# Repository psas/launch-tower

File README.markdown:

PSAS Launch Tower Computer (LTC)
================================

PSAS has had three generations of launch tower computers:

- [LTC v1 (2005-2012)](http://psas.pdx.edu/Lv2LaunchTowerElectronics/)
   - PC-104+ 486 running Linux 2.4 talking CAN to PIC18F-based boards with relays and analog
   - Lucent "Wavelan" PCMCIA WiFi card
   - 12V SLA battery powered with 30W solar panel
   - Metal IP66 case on independent
- [LTC v2 (2012 - 2014)](http://psas.pdx.edu/GroundTeamHome/launch_tower_v2/)
   - Beagle board talking USB to Phidget relay and analog boards
   - Alpha WiFi board
   - Ethernet umbilical cord
   - 12V SLA battery powered with 30W solar panel
   - Medium sized plastic IP67 enclosure
- LTC v3
   - BeagleBone Black using GPIO and analog mounted on a single custom carrier PCB
   - 14.7V LiPo pack with solar charger.
   - Smaller case

This repo contains everything related to the launch tower computer
(LTC), with the exception of the userspace software, which is
contained in the [launch-tower-comm repo](https://github.com/psas/launch-tower-comm).

Contents
========

- doc
   - Documentation, what there is of it.

- eagle
   - Schematics and PCB layouts, made with [Eagle](http://www.cadsoftusa.com/).

- laser_cut_drawings
   - Line art of the power and ignition boards' mounting panels, suitable for use with a laser cutter.

- ltc3
   - Everything related to the design and manufacture of the third generation launch tower computer, LTC3.

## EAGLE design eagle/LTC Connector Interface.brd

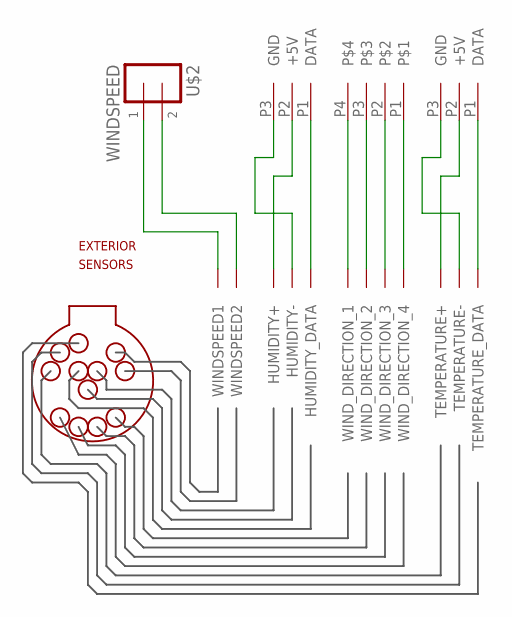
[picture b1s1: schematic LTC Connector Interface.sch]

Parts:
HUMIDITY: MOLEX-3
TEMP: MOLEX-3
U$1: LAYOUT-LEMO-12PIN; LEMO-12
U$2: WINDSPEED; SCREW-TERM-5MM
WINDDIRECTION: MOLEX-4

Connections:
unnamed: U$1.P6 (WINDSPEED1), U$2.1
unnamed: U$1.P5 (WINDSPEED2), U$2.2
unnamed: U$1.P3 (WIND_DIRECTION_3), WINDDIRECTION.P2
unnamed: U$1.P10 (WIND_DIRECTION_2), WINDDIRECTION.P3
unnamed: U$1.P11 (WIND_DIRECTION_1), WINDDIRECTION.P4
unnamed: U$1.P4 (WIND_DIRECTION_4), WINDDIRECTION.P1
unnamed: TEMP.P1 (DATA), U$1.P1 (TEMPERATURE_DATA)
unnamed: TEMP.P3 (GND), U$1.P8 (TEMPERATURE-)
unnamed: TEMP.P2 (+5V), U$1.P7 (TEMPERATURE+)
unnamed: HUMIDITY.P1 (DATA), U$1.P2 (HUMIDITY_DATA)
unnamed: HUMIDITY.P2 (+5V), U$1.P12 (HUMIDITY+)
unnamed: HUMIDITY.P3 (GND), U$1.P9 (HUMIDITY-)

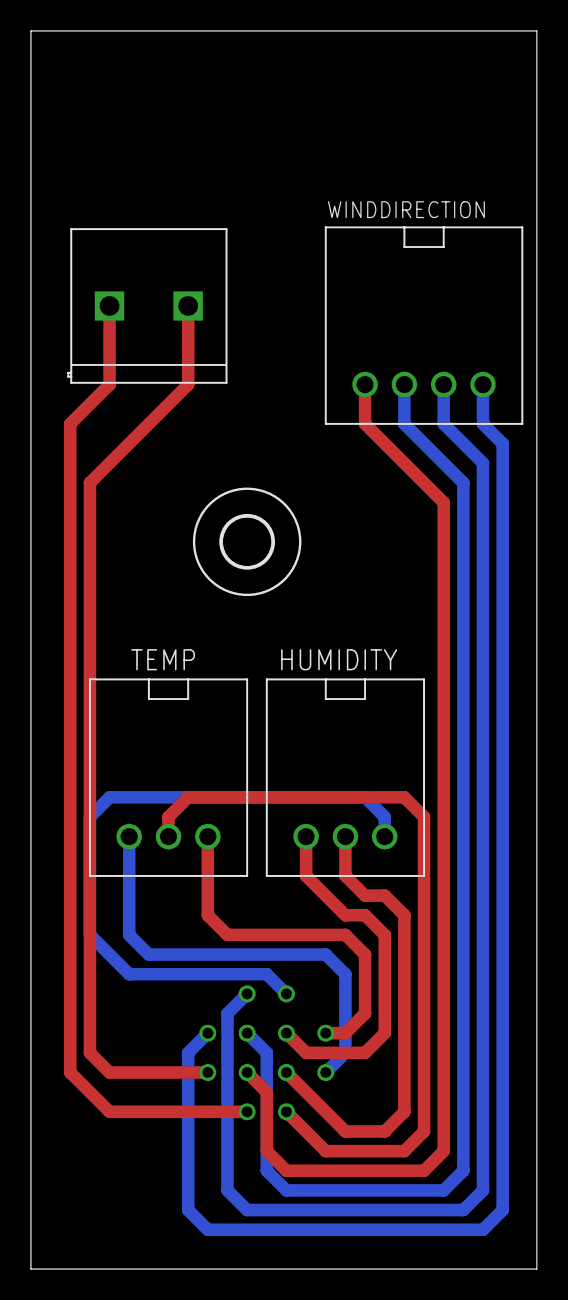
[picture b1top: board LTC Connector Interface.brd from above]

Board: 2 copper layers, 32.7 x 80.0 mm, 6 parts (0 on the bottom side), 12 nets.

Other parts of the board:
U$3: 3,2

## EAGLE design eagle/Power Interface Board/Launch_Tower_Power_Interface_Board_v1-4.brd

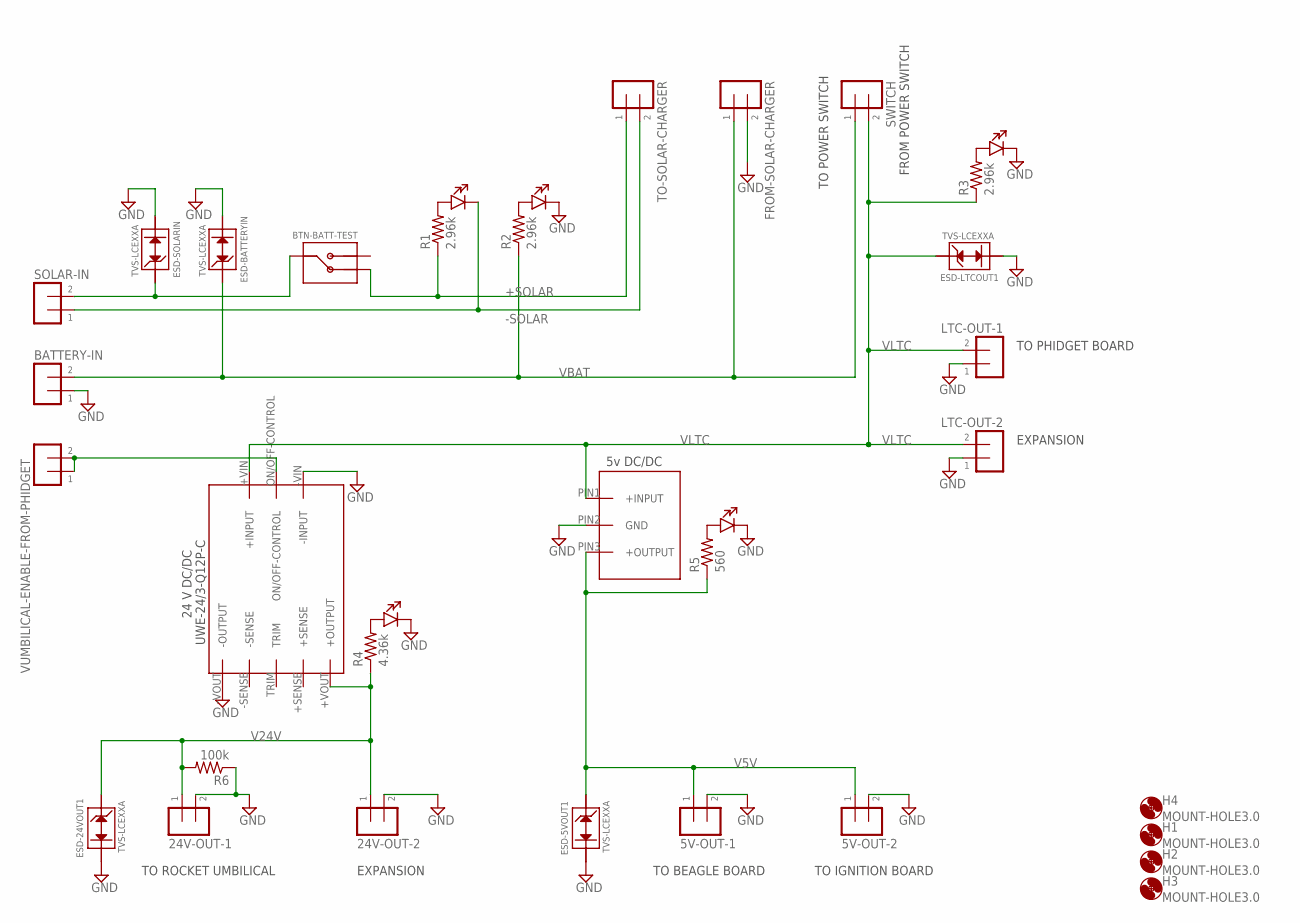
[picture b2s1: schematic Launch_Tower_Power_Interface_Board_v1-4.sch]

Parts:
5V-OUT-1, 5V-OUT-2, 24V-OUT-1, 24V-OUT-2: SCREW-TERMINAL-5MM; SCREW-TERM-5MM
BATTERY-IN: SCREW-TERMINAL-5MM; SCREW-TERM-5MM
BTN-BATT-TEST: BUTTON-107-3006-EVX; BUTTON-1
DC1: DC/DC_CONV_5V; OKI-SIP
DC2: UWE-24/3-Q12P-C; UWE
ESD-5VOUT1, ESD-24VOUT1: TVS-LCEXXA; D0-201
ESD-BATTERYIN: TVS-LCEXXA; D0-201
ESD-LTCOUT1: TVS-LCEXXA; D0-201
ESD-SOLARIN: TVS-LCEXXA; D0-201
FROM-SOLAR-CHARGER: SCREW-TERMINAL-5MM; SCREW-TERM-5MM
H1, H2, H3, H4: MOUNT-HOLE3.0; 3,0
LED-5V-DC/DC, LED-24V-DC/DC: LED-550-XX04; LED-550
LED-BATTERY-IN: LED-550-XX04; LED-550
LED-SOLAR-IN: LED-550-XX04; LED-550
LED-SWITCH-IN: LED-550-XX04; LED-550
LTC-OUT-1, LTC-OUT-2: SCREW-TERMINAL-5MM; SCREW-TERM-5MM
R1, R2, R3: 2.96k; 0805-B
R4: 4.36k; 0805-B
R5: 560; 0805-B
R6: 100k; 0805-B
SOLAR-IN: SCREW-TERMINAL-5MM; SCREW-TERM-5MM
SWITCH: SCREW-TERMINAL-5MM; SCREW-TERM-5MM
TO-SOLAR-CHARGER: SCREW-TERMINAL-5MM; SCREW-TERM-5MM
VUMBILICAL-ENABLE-FROM-PHIDGET: SCREW-TERMINAL-5MM; SCREW-TERM-5MM

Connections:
+SOLAR: BTN-BATT-TEST.NC, R1.1, TO-SOLAR-CHARGER.1
-SOLAR: LED-SOLAR-IN.CATHODE, SOLAR-IN.1, TO-SOLAR-CHARGER.2
GND: 5V-OUT-1.2, 5V-OUT-2.2, 24V-OUT-1.2, 24V-OUT-2.2, BATTERY-IN.1, DC1.PIN2 (GND), DC2.-VIN (-INPUT), DC2.-VOUT (-OUTPUT), ESD-5VOUT1.CATHODE, ESD-24VOUT1.CATHODE, ESD-BATTERYIN.CATHODE, ESD-LTCOUT1.CATHODE, ESD-SOLARIN.CATHODE, FROM-SOLAR-CHARGER.2, LED-5V-DC/DC.CATHODE, LED-24V-DC/DC.CATHODE, LED-BATTERY-IN.CATHODE, LED-SWITCH-IN.CATHODE, LTC-OUT-1.1, LTC-OUT-2.1, R6.1
GPIO: DC2.ON/OFF-CONTROL, VUMBILICAL-ENABLE-FROM-PHIDGET.1, VUMBILICAL-ENABLE-FROM-PHIDGET.2
unnamed: LED-SOLAR-IN.ANODE, R1.2
unnamed: LED-BATTERY-IN.ANODE, R2.2
unnamed: LED-SWITCH-IN.ANODE, R3.2
unnamed: LED-5V-DC/DC.ANODE, R5.2
unnamed: LED-24V-DC/DC.ANODE, R4.2
unnamed: BTN-BATT-TEST.COMMON, ESD-SOLARIN.ANODE, SOLAR-IN.2
V5V: 5V-OUT-1.1, 5V-OUT-2.1, DC1.PIN3 (+OUTPUT), ESD-5VOUT1.ANODE, R5.1
V24V: 24V-OUT-1.1, 24V-OUT-2.1, DC2.+VOUT (+OUTPUT), ESD-24VOUT1.ANODE, R4.1, R6.2
VBAT: BATTERY-IN.2, ESD-BATTERYIN.ANODE, FROM-SOLAR-CHARGER.1, R2.1, SWITCH.1
VLTC: DC1.PIN1 (+INPUT), DC2.+VIN (+INPUT), ESD-LTCOUT1.ANODE, LTC-OUT-1.2, LTC-OUT-2.2, R3.1, SWITCH.2

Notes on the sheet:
5v DC/DC
TO POWER SWITCH
FROM POWER SWITCH
EXPANSION
TO PHIDGET BOARD
TO BEAGLE BOARD
TO IGNITION BOARD
UWE-24/3-Q12P-C
TO ROCKET UMBILICAL
24 V DC/DC

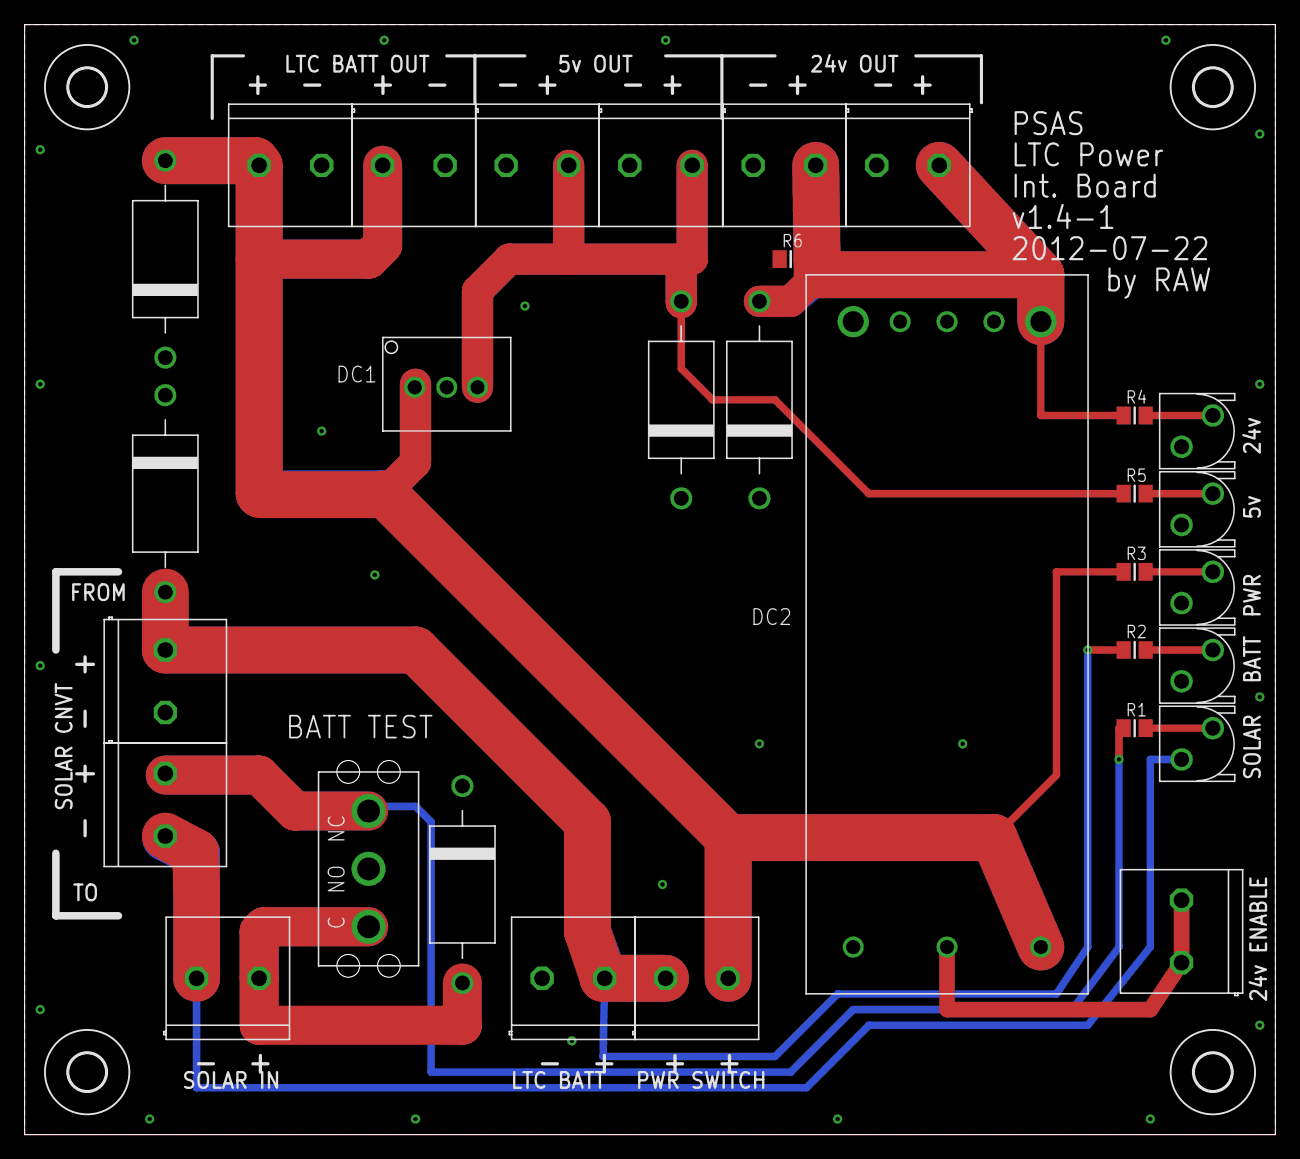
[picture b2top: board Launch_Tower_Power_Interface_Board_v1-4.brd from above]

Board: 2 copper layers, 101.6 x 90.2 mm, 35 parts (0 on the bottom side), 14 nets.

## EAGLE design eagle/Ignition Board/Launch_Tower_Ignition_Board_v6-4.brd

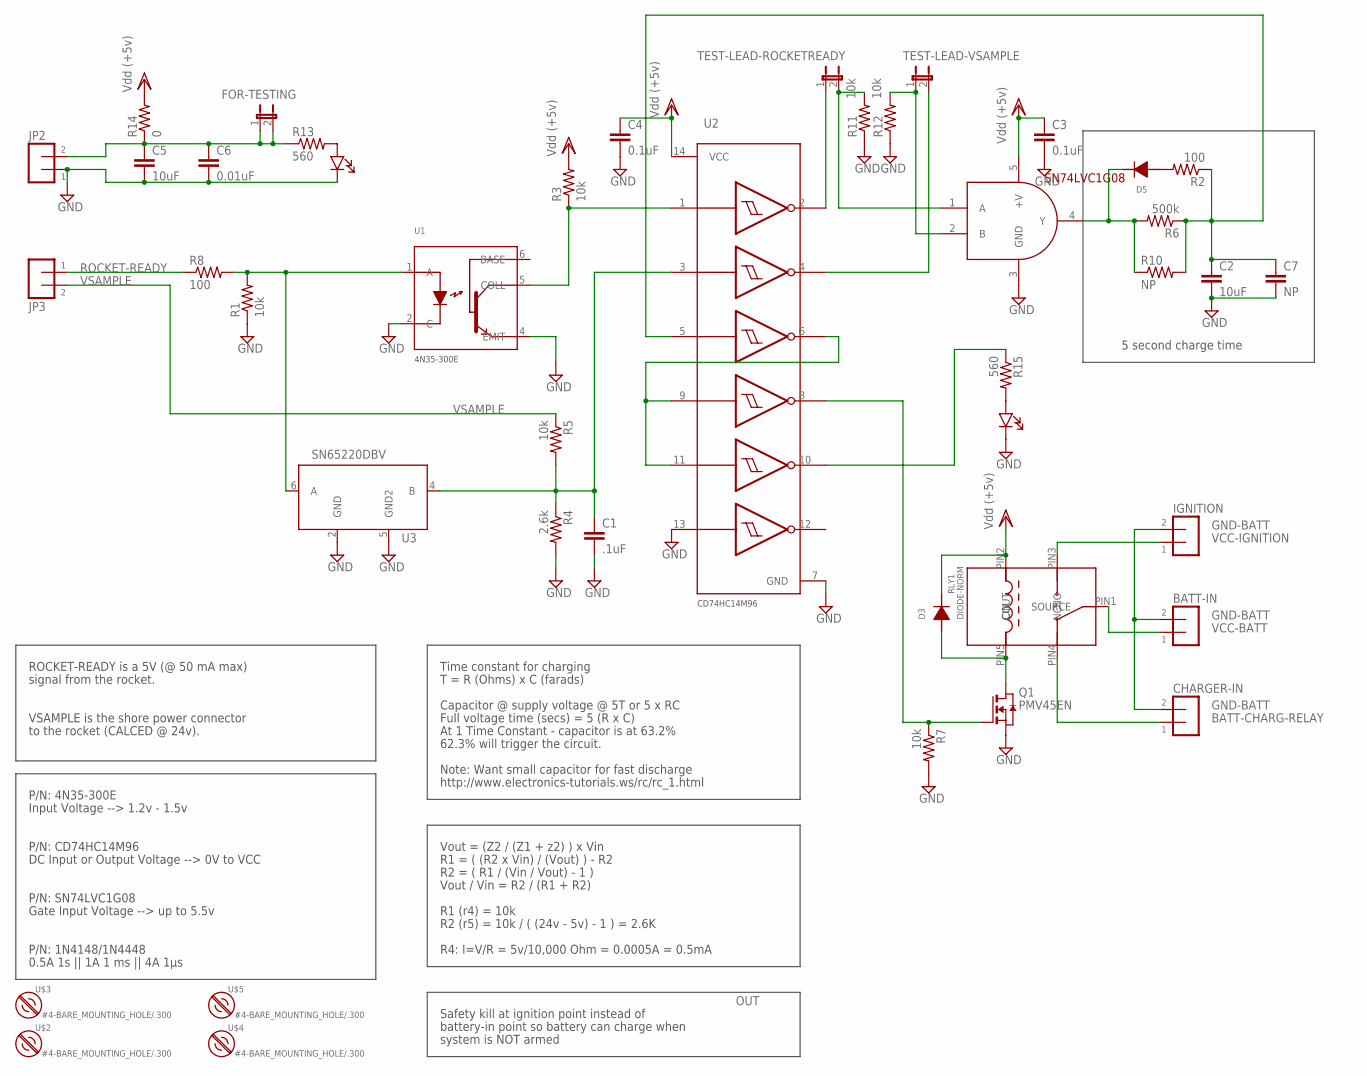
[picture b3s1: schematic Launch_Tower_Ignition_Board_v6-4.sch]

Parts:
BATT-IN: SCREW-TERMINAL-5MM; SCREW-TERM-5MM
C1: .1uF; 0805-B
C2, C5: 10uF; 0805-B
C3, C4: 0.1uF; 0805-B
C6: 0.01uF; 0805-B
C7: NP; CAP-PTH-SMALL
CHARGER-IN: SCREW-TERMINAL-5MM; SCREW-TERM-5MM
D3, D5: DIODE-NORM; DIODE
FOR-TESTING: JUMPER-2PTH; 1X02
IGNITION: SCREW-TERMINAL-5MM; SCREW-TERM-5MM
JP2, JP3: SCREW-TERMINAL-5MM; SCREW-TERM-5MM
LED-POWER-INDICATOR, LED-POWER-INDICATOR1: LED-550-XX04; LED-550
Q1: PMV45EN; SOT23
R1, R3, R5, R7, R11, R12: 10k; 0805-B
R2, R8: 100; 0805-B
R4: 2.6k; 0805-B
R6: 500k; 0805-B
R10: NP; 0207/10
R13, R15: 560; 0805-B
R14: 0; 0805-B
RLY1: RELAY-2; G5LA
TEST-LEAD-ROCKETREADY: JUMPER-2PTH; 1X02
TEST-LEAD-VSAMPLE: JUMPER-2PTH; 1X02
U1: OPTOISOLATOR; 4N35-300E
U2: INVERT GATES; INVERTSOIC14
U3: SN65220DBV; SOT23-6L
U4: AND GATE; SOT23-5
U$2, U$3, U$4, U$5: #4-BARE_MOUNTING_HOLE/.300; #4/.300-BARE+STD_NUT_OR_STAR_WASHER

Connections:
BATT-CHARG-RELAY: CHARGER-IN.1, RLY1.PIN4 (NC)
GND-BATT: BATT-IN.2, CHARGER-IN.2, IGNITION.2
unnamed: R12.2, TEST-LEAD-VSAMPLE.1, U4.2 (B)
unnamed: LED-POWER-INDICATOR.ANODE, R13.2
unnamed: R3.1, U1.5 (COLL), U2.1 (1A)
unnamed: JP3.1, R8.1
unnamed: R11.2, TEST-LEAD-ROCKETREADY.2, U4.1 (A)
unnamed: TEST-LEAD-VSAMPLE.2, U2.4 (2Y)
unnamed: C1.1, R4.1, R5.2, U2.3 (2A), U3.4 (B)
unnamed: D5.A, R2.2
unnamed: D3.A, Q1.3 (D), RLY1.PIN5 (CIN)
unnamed: Q1.1 (G), R7.1, U2.8 (4Y)
unnamed: TEST-LEAD-ROCKETREADY.1, U2.2 (1Y)
unnamed: C5.1, C6.1, FOR-TESTING.1, FOR-TESTING.2, JP2.2, R13.1, R14.1
unnamed: D5.C, R6.2, R10.1, U4.4 (Y)
unnamed: R15.1, U2.10 (5Y)
unnamed: C2.1, C7.1, R2.1, R6.1, R10.2, U2.5 (3A)
unnamed: LED-POWER-INDICATOR1.ANODE, R15.2
N-NOT2: U2.6 (3Y), U2.9 (4A), U2.11 (5A)
NAME: C1.2, C2.2, C3.2, C4.2, C5.2, C6.2, C7.2, JP2.1, LED-POWER-INDICATOR.CATHODE, LED-POWER-INDICATOR1.CATHODE, Q1.2 (S), R1.1, R4.2, R7.2, R11.1, R12.1, U1.2 (C), U1.4 (EMIT), U2.7 (GND), U2.13 (6A), U3.2 (GND), U3.5 (GND2), U4.3 (GND)
ROCKET-READY: R1.2, R8.2, U1.1 (A), U3.6 (A)
VCC-BATT: BATT-IN.1, RLY1.PIN1 (SOURCE)
VCC-IGNITION: IGNITION.1, RLY1.PIN3 (NO)
VDD: C3.1, C4.1, D3.C, R3.2, R14.2, RLY1.PIN2 (COUT), U2.14 (VCC), U4.5 (+V)
VSAMPLE: JP3.2, R5.1

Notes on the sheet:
ROCKET-READY is a 5V (@ 50 mA max)
signal from the rocket.
VSAMPLE is the shore power connector
to the rocket (CALCED @ 24v).
OUT
R4: I=V/R = 5v/10,000 Ohm = 0.0005A = 0.5mA
Time constant for charging
T = R (Ohms) x C (farads)
Capacitor @ supply voltage @ 5T or 5 x RC
Full voltage time (secs) = 5 (R x C)
Note: Want small capacitor for fast discharge
Vout = (Z2 / (Z1 + z2) ) x Vin
R1 = ( (R2 x Vin) / (Vout) ) - R2
R2 = ( R1 / (Vin / Vout) - 1 )
Vout / Vin = R2 / (R1 + R2)
0.5A 1s || 1A 1 ms || 4A 1μs
R1 (r4) = 10k
Gate Input Voltage --> up to 5.5v
DC Input or Output Voltage --> 0V to VCC
P/N: SN74LVC1G08
P/N: CD74HC14M96
P/N: 4N35-300E
Input Voltage --> 1.2v - 1.5v
R2 (r5) = 10k / ( (24v - 5v) - 1 ) = 2.6K
P/N: 1N4148/1N4448
http://www.electronics-tutorials.ws/rc/rc_1.html
5 second charge time
Safety kill at ignition point instead of
battery-in point so battery can charge when
system is NOT armed
At 1 Time Constant - capacitor is at 63.2%
62.3% will trigger the circuit.

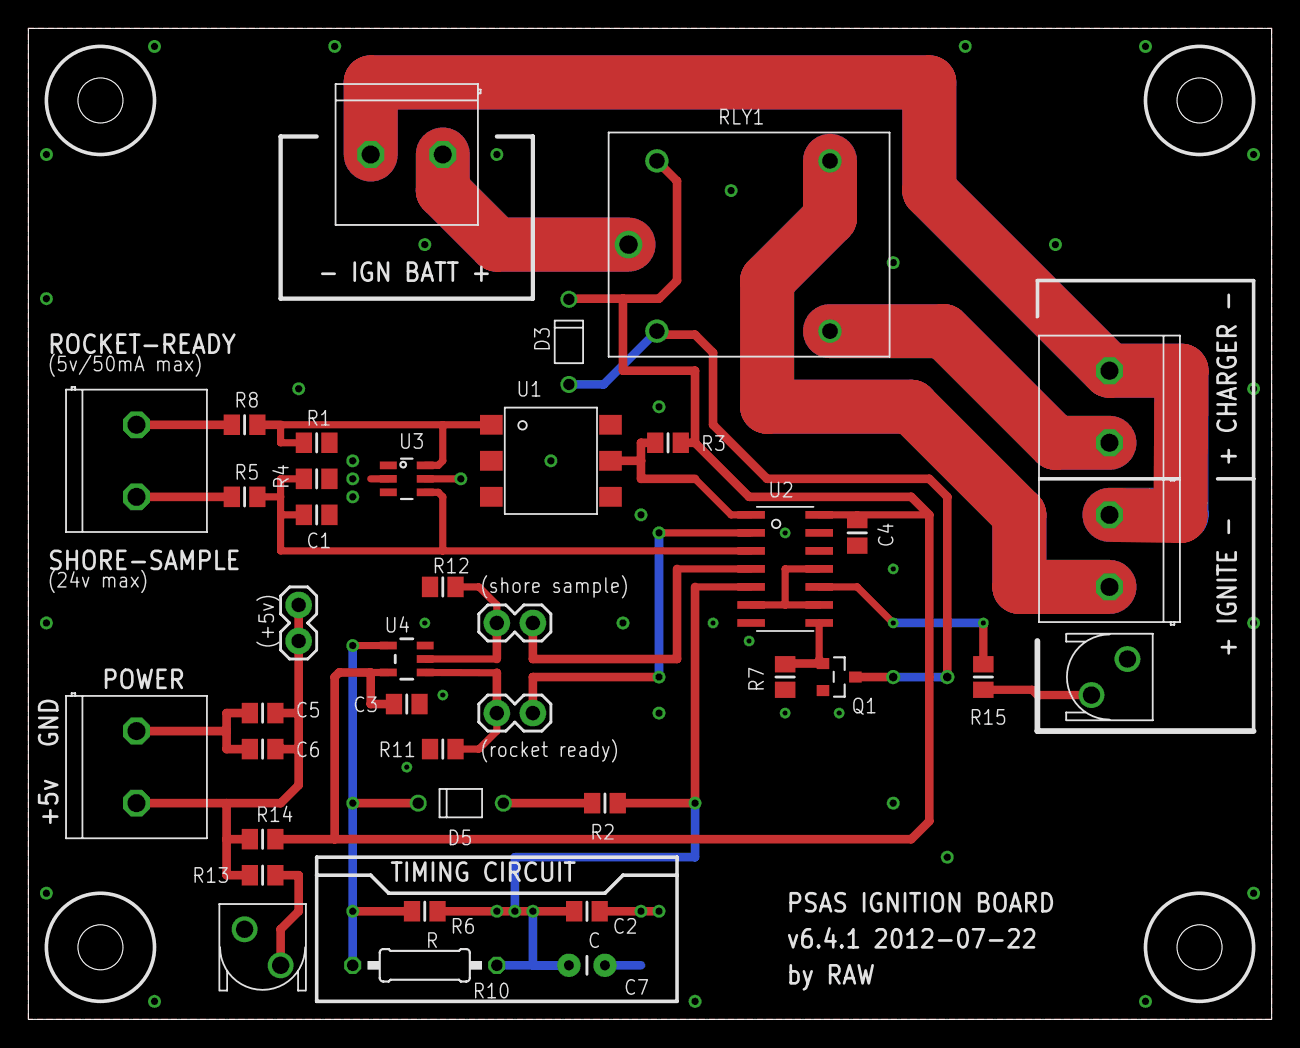
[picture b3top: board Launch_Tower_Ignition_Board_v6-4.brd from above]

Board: 2 copper layers, 87.6 x 69.8 mm, 43 parts (0 on the bottom side), 25 nets.

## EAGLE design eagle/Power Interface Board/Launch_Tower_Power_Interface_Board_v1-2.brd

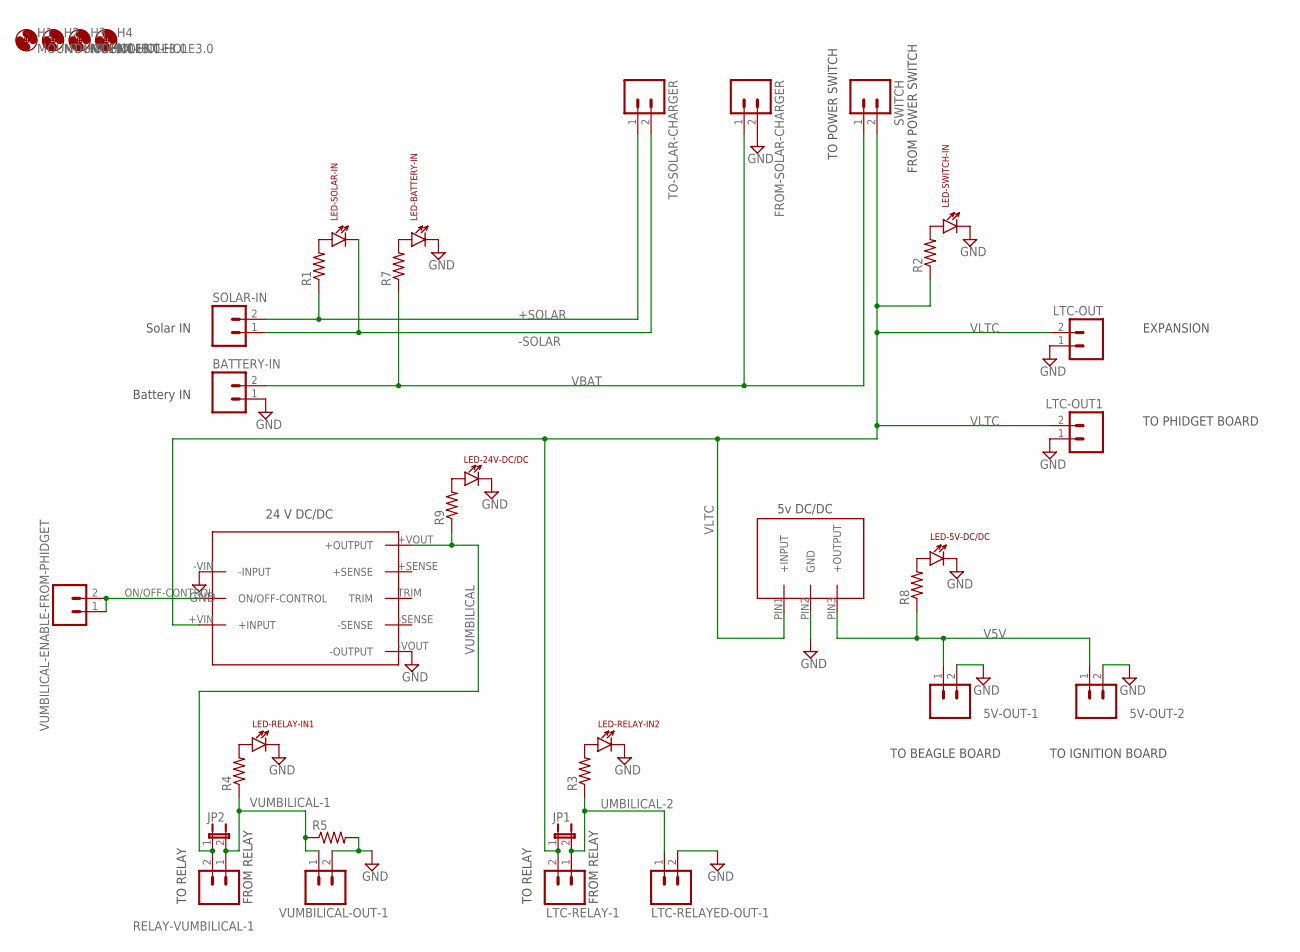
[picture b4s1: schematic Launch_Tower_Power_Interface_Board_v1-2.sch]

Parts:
5V-OUT-1, 5V-OUT-2: M025MM; SCREWTERMINAL-5MM-2
BATTERY-IN: M025MM; SCREWTERMINAL-5MM-2
FROM-SOLAR-CHARGER: M025MM; SCREWTERMINAL-5MM-2
H1, H2, H3, H4: MOUNT-HOLE3.0; 3,0
JP1, JP2: JUMPER-2PTH; 1X02
LED-5V-DC/DC, LED-24V-DC/DC: LTE-302
LED-BATTERY-IN: LTE-302
LED-RELAY-IN1, LED-RELAY-IN2: LTE-302
LED-SOLAR-IN: LTE-302
LED-SWITCH-IN: LTE-302
LTC-OUT, LTC-OUT1: M025MM; SCREWTERMINAL-5MM-2
LTC-RELAY-1: M025MM; SCREWTERMINAL-5MM-2
LTC-RELAYED-OUT-1: M025MM; SCREWTERMINAL-5MM-2
R1, R2, R3, R4, R5, R7, R8, R9: RESISTORPTH-1/2W; AXIAL-0.5
RELAY-VUMBILICAL-1: M025MM; SCREWTERMINAL-5MM-2
SOLAR-IN: M025MM; SCREWTERMINAL-5MM-2
SWITCH: M025MM; SCREWTERMINAL-5MM-2
TO-SOLAR-CHARGER: M025MM; SCREWTERMINAL-5MM-2
U$1: DC/DC_CONV_24V; UWE
U$2: DC/DC_CONV_5V; OKI-SIP
VUMBILICAL-ENABLE-FROM-PHIDGET: M023.5MM; SCREWTERMINAL-3.5MM-2
VUMBILICAL-OUT-1: M025MM; SCREWTERMINAL-5MM-2

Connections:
+SOLAR: R1.P$1 (1), SOLAR-IN.2, TO-SOLAR-CHARGER.1
-SOLAR: LED-SOLAR-IN.C, SOLAR-IN.1, TO-SOLAR-CHARGER.2
GND: 5V-OUT-1.2, 5V-OUT-2.2, BATTERY-IN.1, FROM-SOLAR-CHARGER.2, LED-5V-DC/DC.C, LED-24V-DC/DC.C, LED-BATTERY-IN.C, LED-RELAY-IN1.C, LED-RELAY-IN2.C, LED-SWITCH-IN.C, LTC-OUT.1, LTC-OUT1.1, LTC-RELAYED-OUT-1.2, R5.P$2 (2), U$1.-VIN (-INPUT), U$1.-VOUT (-OUTPUT), U$2.PIN2 (GND), VUMBILICAL-OUT-1.2
GPIO: U$1.ON/OFF-CONTROL, VUMBILICAL-ENABLE-FROM-PHIDGET.1, VUMBILICAL-ENABLE-FROM-PHIDGET.2
unnamed: LED-SOLAR-IN.A, R1.P$2 (2)
unnamed: LED-SWITCH-IN.A, R2.P$2 (2)
unnamed: LED-RELAY-IN2.A, R3.P$2 (2)
unnamed: LED-BATTERY-IN.A, R7.P$2 (2)
unnamed: LED-5V-DC/DC.A, R8.P$2 (2)
unnamed: LED-RELAY-IN1.A, R4.P$2 (2)
unnamed: LED-24V-DC/DC.A, R9.P$2 (2)
UMBILICAL-2: JP1.2, LTC-RELAY-1.1, LTC-RELAYED-OUT-1.1, R3.P$1 (1)
V5V: 5V-OUT-1.1, 5V-OUT-2.1, R8.P$1 (1), U$2.PIN3 (+OUTPUT)
VBAT: BATTERY-IN.2, FROM-SOLAR-CHARGER.1, R7.P$1 (1), SWITCH.1
VLTC: JP1.1, LTC-OUT.2, LTC-OUT1.2, LTC-RELAY-1.2, R2.P$1 (1), SWITCH.2, U$1.+VIN (+INPUT), U$2.PIN1 (+INPUT)
VUMBILICAL: JP2.1, R9.P$1 (1), RELAY-VUMBILICAL-1.2, U$1.+VOUT (+OUTPUT)
VUMBILICAL-1: JP2.2, R4.P$1 (1), R5.P$1 (1), RELAY-VUMBILICAL-1.1, VUMBILICAL-OUT-1.1

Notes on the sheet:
Solar IN
Battery IN
5v DC/DC
TO RELAY
TO POWER SWITCH
FROM POWER SWITCH
FROM RELAY
EXPANSION
TO PHIDGET BOARD
TO BEAGLE BOARD
TO IGNITION BOARD
24 V DC/DC

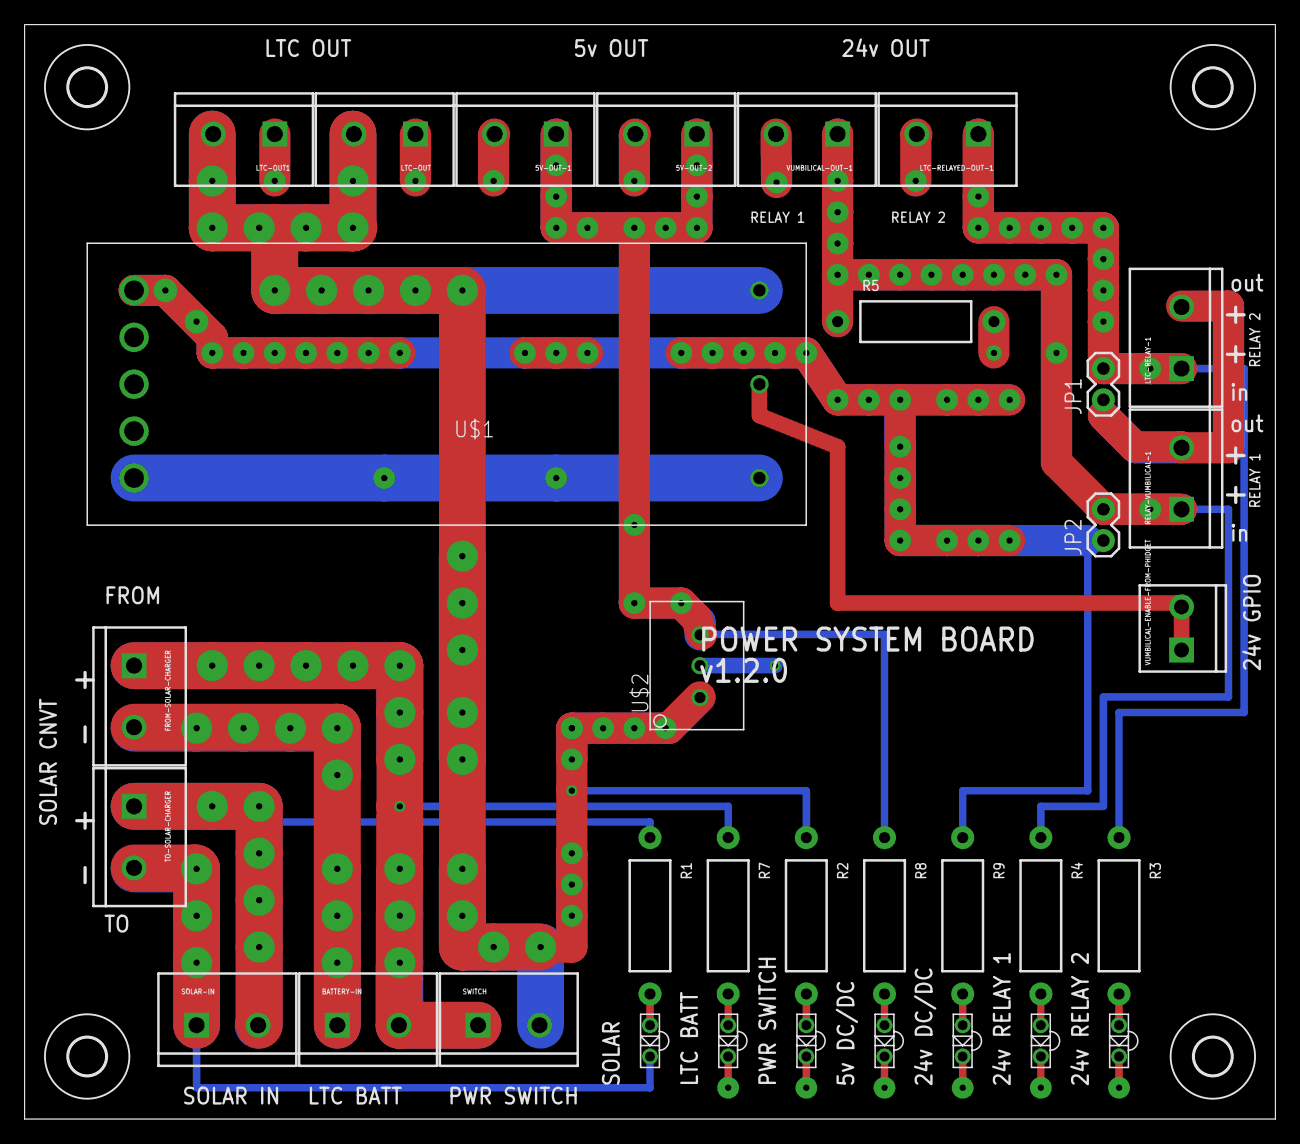
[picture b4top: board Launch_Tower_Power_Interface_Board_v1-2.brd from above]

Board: 2 copper layers, 101.6 x 88.9 mm, 37 parts (0 on the bottom side), 17 nets.

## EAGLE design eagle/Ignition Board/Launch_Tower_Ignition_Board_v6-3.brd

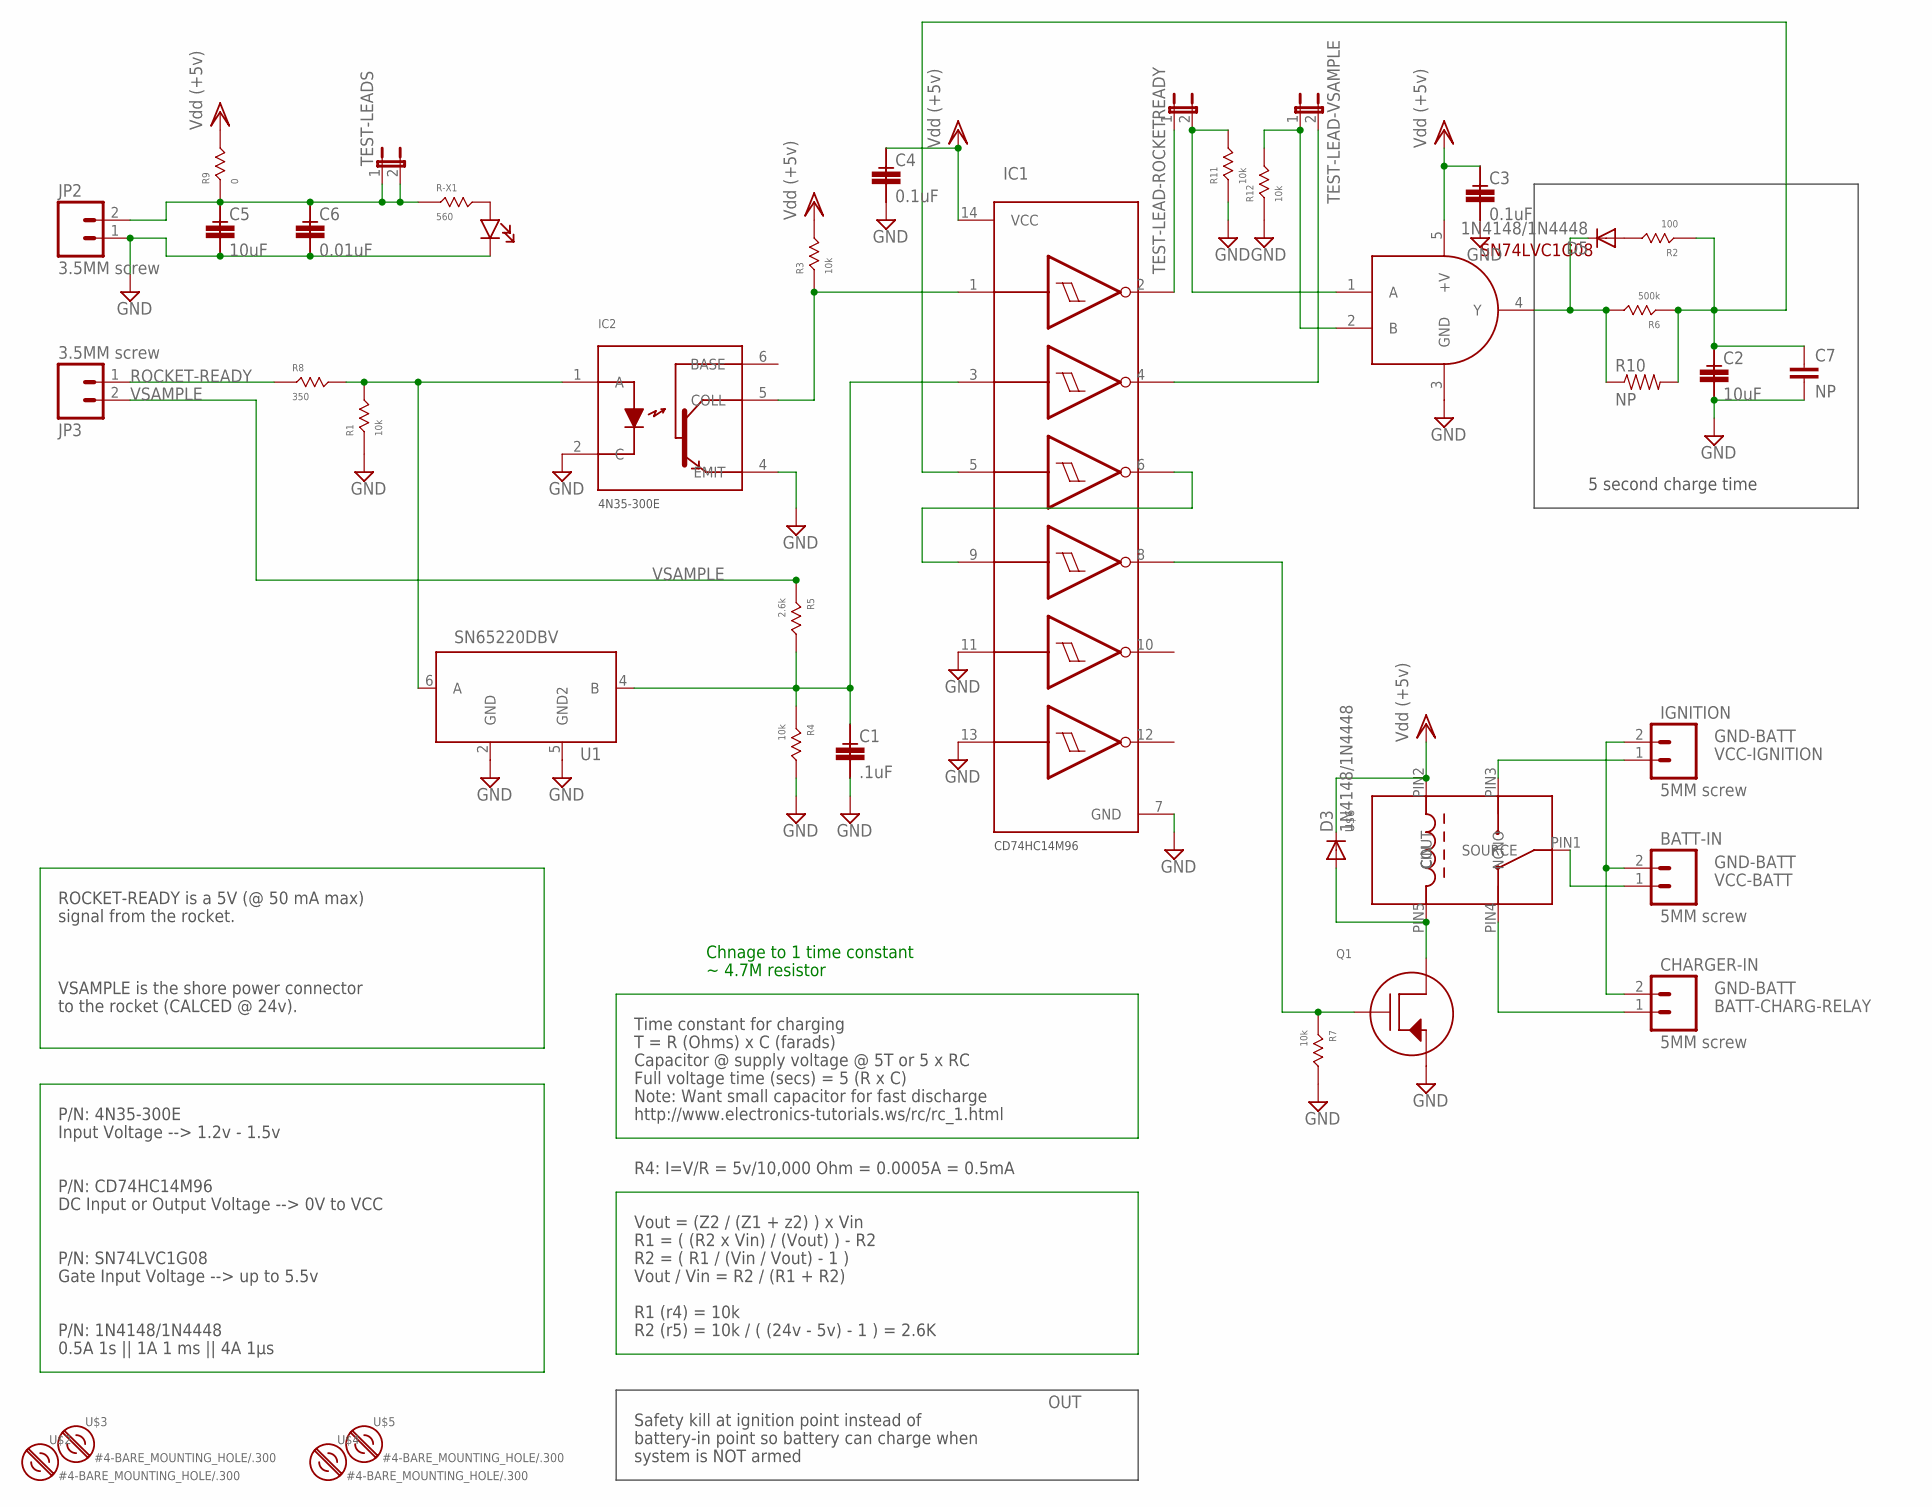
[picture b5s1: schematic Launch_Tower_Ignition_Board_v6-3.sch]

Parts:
BATT-IN: 5MM screw; SCREWTERMINAL-5MM-2
C1: .1uF; 0805
C2, C5: 10uF; 0805
C3, C4: 0.1uF; 0805
C6: 0.01uF; 0805
C7: NP; CAP-PTH-SMALL
CHARGER-IN: 5MM screw; SCREWTERMINAL-5MM-2
D3, D5: 1N4148/1N4448; DIODE-1N4001
IC1: INVERT GATES; INVERTSOIC14
IC2: OPTOISOLATOR; 4N35-300E
IGNITION: 5MM screw; SCREWTERMINAL-5MM-2
JP2, JP3: 3.5MM screw; SCREWTERMINAL-3.5MM-2
LED-POWER-INDICATOR: LED-550-XX04; LED-550
Q1: NMOSFET; FETSO-8
R1, R3, R4, R7, R11, R12: 10k; 0805
R2: 100; 0805
R5: 2.6k; 0805
R6: 500k; 0805
R8: 350; 0805
R9: 0; 0805
R10: NP; AXIAL-0.4
R-X1: 560; 0805
TEST-LEAD-ROCKETREADY: JUMPER-2PTH; 1X02
TEST-LEAD-VSAMPLE: JUMPER-2PTH; 1X02
TEST-LEADS: JUMPER-2PTH; 1X02
U1: SN65220DBV; SOT23-6L
U$1: AND GATE; SOT23-5
U$2, U$3, U$4, U$5: #4-BARE_MOUNTING_HOLE/.300; #4/.300-BARE+STD_NUT_OR_STAR_WASHER
U$6: RELAY-2; G5LA

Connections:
BATT-CHARG-RELAY: CHARGER-IN.1, U$6.PIN4 (NC)
GND: C1.CATHODE, C2.CATHODE, C3.CATHODE, C4.CATHODE, C5.CATHODE, C6.CATHODE, C7.2, IC1.7 (GND), IC1.11 (5A), IC1.13 (6A), IC2.2 (C), IC2.4 (EMIT), JP2.1, LED-POWER-INDICATOR.CATHODE, Q1.1 (SOURCE), R1.ANODE, R4.CATHODE, R7.CATHODE, R11.ANODE, R12.ANODE, U1.2 (GND), U1.5 (GND2), U$1.3 (GND)
GND-BATT: BATT-IN.2, CHARGER-IN.2, IGNITION.2
unnamed: R12.CATHODE, TEST-LEAD-VSAMPLE.1, U$1.2 (B)
unnamed: LED-POWER-INDICATOR.ANODE, R-X1.CATHODE
unnamed: IC1.1 (1A), IC2.5 (COLL), R3.ANODE
unnamed: JP3.1, R8.ANODE
unnamed: R11.CATHODE, TEST-LEAD-ROCKETREADY.2, U$1.1 (A)
unnamed: IC1.4 (2Y), TEST-LEAD-VSAMPLE.2
unnamed: C1.ANODE, IC1.3 (2A), R4.ANODE, R5.CATHODE, U1.4 (B)
unnamed: D5.A, R2.CATHODE
unnamed: D3.A, Q1.5 (DRAIN), U$6.PIN5 (CIN)
unnamed: IC1.8 (4Y), Q1.4 (GATE), R7.ANODE
unnamed: IC1.2 (1Y), TEST-LEAD-ROCKETREADY.1
unnamed: C5.ANODE, C6.ANODE, JP2.2, R9.ANODE, R-X1.ANODE, TEST-LEADS.1, TEST-LEADS.2
unnamed: D5.C, R6.CATHODE, R10.P$1 (1), U$1.4 (Y)
unnamed: C2.ANODE, C7.1, IC1.5 (3A), R2.ANODE, R6.ANODE, R10.P$2 (2)
N-NOT2: IC1.6 (3Y), IC1.9 (4A)
ROCKET-READY: IC2.1 (A), R1.CATHODE, R8.CATHODE, U1.6 (A)
VCC-BATT: BATT-IN.1, U$6.PIN1 (SOURCE)
VCC-IGNITION: IGNITION.1, U$6.PIN3 (NO)
VDD: C3.ANODE, C4.ANODE, D3.C, IC1.14 (VCC), R3.CATHODE, R9.CATHODE, U$1.5 (+V), U$6.PIN2 (COUT)
VSAMPLE: JP3.2, R5.ANODE

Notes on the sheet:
ROCKET-READY is a 5V (@ 50 mA max)
signal from the rocket.
VSAMPLE is the shore power connector
to the rocket (CALCED @ 24v).
OUT
R4: I=V/R = 5v/10,000 Ohm = 0.0005A = 0.5mA
Time constant for charging
T = R (Ohms) x C (farads)
Capacitor @ supply voltage @ 5T or 5 x RC
Full voltage time (secs) = 5 (R x C)
Note: Want small capacitor for fast discharge
Vout = (Z2 / (Z1 + z2) ) x Vin
R1 = ( (R2 x Vin) / (Vout) ) - R2
R2 = ( R1 / (Vin / Vout) - 1 )
Vout / Vin = R2 / (R1 + R2)
0.5A 1s || 1A 1 ms || 4A 1μs
R1 (r4) = 10k
Gate Input Voltage --> up to 5.5v
DC Input or Output Voltage --> 0V to VCC
P/N: SN74LVC1G08
P/N: CD74HC14M96
P/N: 4N35-300E
Input Voltage --> 1.2v - 1.5v
R2 (r5) = 10k / ( (24v - 5v) - 1 ) = 2.6K
P/N: 1N4148/1N4448
http://www.electronics-tutorials.ws/rc/rc_1.html
5 second charge time
Chnage to 1 time constant
~ 4.7M resistor
Safety kill at ignition point instead of
battery-in point so battery can charge when
system is NOT armed

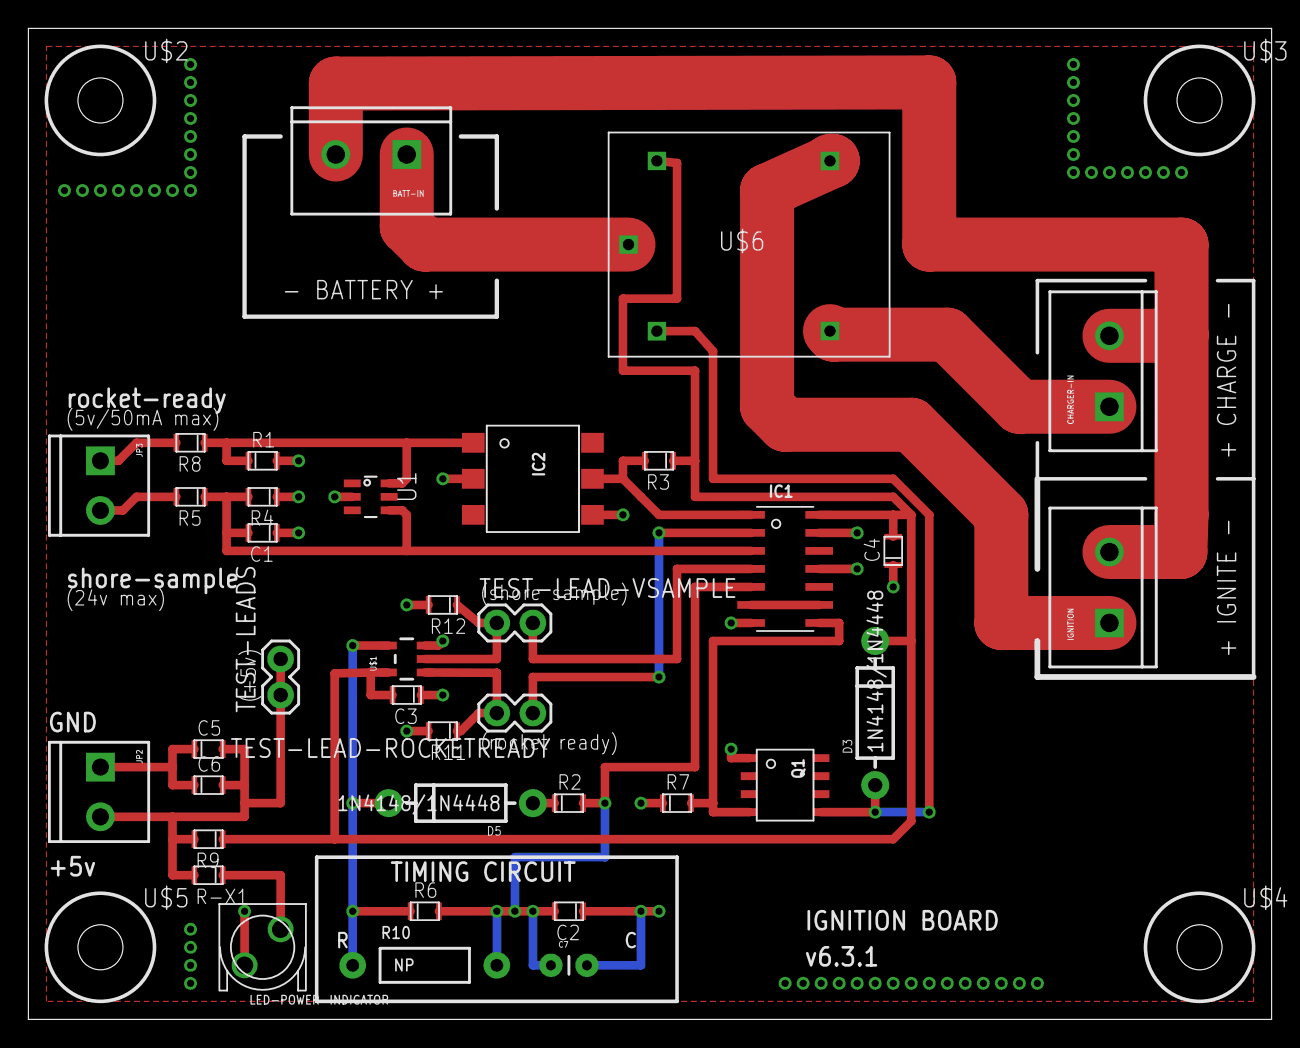
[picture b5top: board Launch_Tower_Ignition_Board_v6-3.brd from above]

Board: 2 copper layers, 87.6 x 69.8 mm, 41 parts (0 on the bottom side), 23 nets.

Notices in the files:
parts and their libraries:
SparkFun: Licensing: CC v3.0 Share-Alike You are welcome to use this library for commercial purposes.
